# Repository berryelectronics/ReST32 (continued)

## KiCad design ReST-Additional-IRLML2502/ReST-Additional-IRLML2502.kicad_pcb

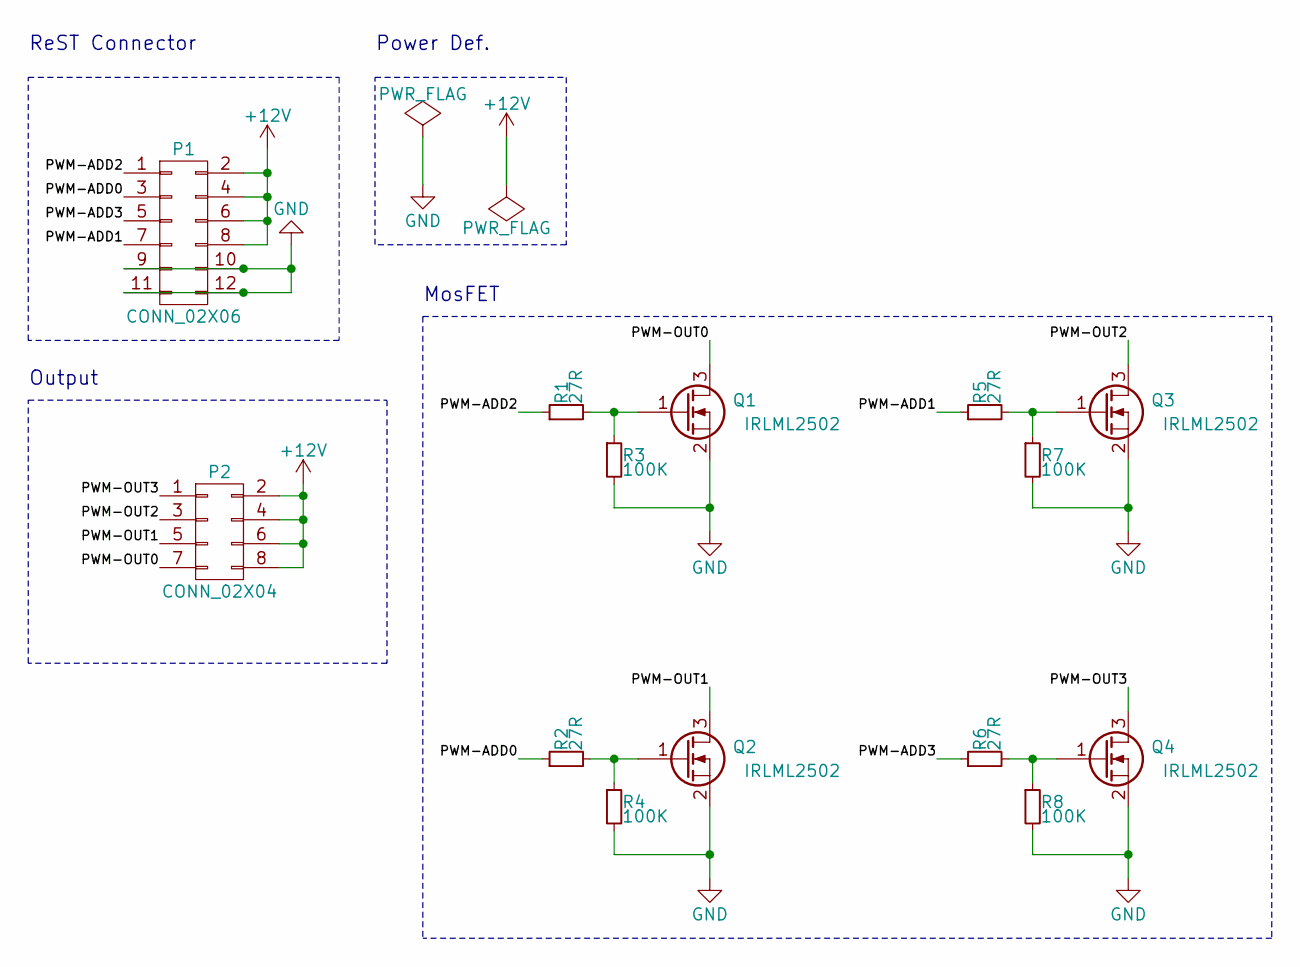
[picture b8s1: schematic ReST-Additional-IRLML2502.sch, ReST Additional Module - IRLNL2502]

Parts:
P1: CONN_02X06; bb02-hp12
P2: CONN_02X04; Pin_Header_Straight_2x04
Q1, Q2, Q3, Q4: IRLML2502; SOT-23
R1, R2, R5, R6: 27R; R_0603_HandSoldering
R3, R4, R7, R8: 100K; R_0603_HandSoldering

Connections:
+12V: P1.2, P1.4, P1.6, P1.8, P2.2, P2.4, P2.6, P2.8
/PWM-ADD0: P1.3, R2.1
/PWM-ADD1: P1.7, R5.1
/PWM-ADD2: P1.1, R1.1
/PWM-ADD3: P1.5, R6.1
/PWM-OUT0: P2.7, Q1.3 (D)
/PWM-OUT1: P2.5, Q2.3 (D)
/PWM-OUT2: P2.3, Q3.3 (D)
/PWM-OUT3: P2.1, Q4.3 (D)
GND: P1.9, P1.10, P1.11, P1.12, Q1.2 (S), Q2.2 (S), Q3.2 (S), Q4.2 (S), R3.2, R4.2, R7.2, R8.2
unnamed: Q1.1 (G), R1.2, R3.1
unnamed: Q2.1 (G), R2.2, R4.1
unnamed: Q3.1 (G), R5.2, R7.1
unnamed: Q4.1 (G), R6.2, R8.1

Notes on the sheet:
ReST Connector
Power Def.
Output
MosFET

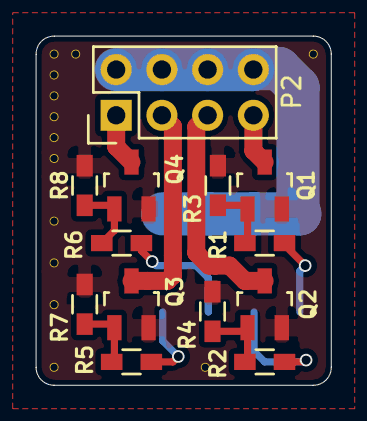
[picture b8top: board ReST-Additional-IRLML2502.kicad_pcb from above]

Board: 2 copper layers, 16.4 x 19.4 mm, 14 parts (1 on the bottom side), 14 nets.

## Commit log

2016-01-24 :space_invader: Added .gitattributes
2016-01-26 Initial Commit
    Added Schematics for Heatbed Module and Mainboard
2016-01-27 Changes Heatbed + Added Driver Board
    Edited Heatbed SMD Footprint from 0805 to 1206, easier to solder for beginners.
    Added Schematic and Netlist for Pololu Driver Board
2016-01-28 Added Libs
2016-01-28 Added all missing Libs.
    You may add them manually.
    Need any suggestion onto how to clean up that library mess. thanks :)
2016-01-29 Layout for Heatbed PCB
    Basic layout for the heatbed pcb is finished. single sided load, so its easier for reflow. need to work on the traces now. size shouldnt change by now.
2016-01-29 Moved Folders + Heatbed PCB Finished
    If there is any problem, please post an issue or write a post on the stm32duino forum. I can assure there is going to be a problem again with the libraries used, would really appreciate it to get som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
2016-01-30 Added Heater Module Schematic + PCB
    Basically its the Heatbed Module but without the fuse (which is going onto the main controller) and without the external VIN, gets power from Pinheader.
    Should be capable of up to 5A if the female pinheader can handle 1A per pin, which seems to be common, but you never know..
2016-01-30 Added Pololu Driver PCB
    Size is 3.5cm * 3.75cm
    Im pretty happy with that size
2016-01-30 Changed minor issues in the Pololu Driver.
    Heatbed wont get much smaller. Finished Dimensions:
    Heatbed: 30,4mm * 47,8mm
    Heater: 29mm * 34,1mm
    Pololu: 36,3mm * 35,2mm
2016-01-30 Added ReST connector to the Mainboard
2016-02-02 Added Additional Module
2016-02-02 Fixed GND Connection on ADD Board
2016-02-02 Saving
2016-02-02 Added Pololu to the Mainboard
2016-02-06 Changes to the mainboard
    removed the pololu connector, added it onboard. added 5V regulator. need to add 3.3V Regulator and more pinout (Bluetooth, SWD, Boot0/Boot1 and more)
2016-02-08 Added Buck & Power Pins
    Buck Converter Added (Still need work on Diode, have to do the math later)
    Power Distribution Pins added (4 Pins of GND 12V 5V 3V3 each) for convenience (Leds and whatnot)
2016-02-08 Added A possible Pinout Table + Removed Pololu Driver Board
2016-02-08 Added PDF
2016-02-08 Added Addition Pinout
2016-02-15 Changed Additional-Board and Pinout
    Sooo... I thought adding multiple Additional Module Boards would be bit much. Looked back at some older projects of mine and thought that using something like the uln2803 would be pretty neat (like 8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
    But using that one resultet in removing many extra pinouts, leaving with only 5 unused pins which will be broken out extra. This may change when the lcd pinout is finished. adding extra pinout for th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
    Also missing: I2C E
2016-02-15 Changed pin naming on excel table
2016-02-15 Added Pin Def. on Mainboard + EEPROM
    FInishing of for today:
    copied the pin def. of the mainboard and added a eeprom (AT24C128)
2016-02-21 Changed ADD Board to use less Pins
    Now only 4 Channels, but everyone ~0.6A capable
2016-02-21 Added LCD 8080 Pinout
2016-02-21 Added Pinout PDF
2016-02-21 Final Version of Main Controller Schematic
2016-02-22 Finishing Footprint connection for Mainboard
2016-02-22 Loaded Netlist into PCB and laid it all out
2016-02-27 PRE-RELEASE Rev. A!
    Yay. I managed to finish the Main PCB over the night, must say, Im happy with it. Things that changed since the last release:
    Heater:
    -Heater Module uses less Pins
    - Much smaller Design now
    Heatbed & Additional Module:
    -Changed distance from Edge to first Pin from 2.5mm to 2mm (will be changed on other boards too)
2016-02-27 Added Images and PDF's
    + Silkscreening
2016-02-27 Added Heatbed 3D Images
2016-02-27 Added PDF for Pinout
    +removed images from logo
2016-02-28 Added Mounting Holes to all Modules
2016-02-28 Missing Mainboard Top PNG
2016-02-28 Added files via upload
2016-02-28 PNG Mainboard
2016-02-28 Added BOM and changed Oscillator to Crystal
2016-02-28 Added Missing Screw Holes on main
2016-02-28 Added SD Card Schematic
2016-03-01 Removed unnecessary Libs and finished SD Card Module
2016-03-05 Finally removed all unnecessary Libs and added Heatsink for 5V Regulator
2016-03-05 Added IRLML2502 Module and added Ground vias everywhere
2016-03-06 Added BOM for all Items + suggested Links
2016-03-06 Added relative paths and linked footprint to a extra repo
    hope i finally fixed the problem with missing libs. will try to add the
    3d views, too
2016-03-07 Finished PCB design, notations and silkscreen
    gonna work to finish a combined design for cheaper pcb cost and put
    everything i need into the bom
2016-03-09 Final release
2016-03-09 Finished Combined PCB and Gerber files
    Combined pcb fits on 10x10cm, breakable and gerbers are finished for elecrow order. will order everything this weekend, lets see if it works.
2016-05-13 Reworked Modules to sit ontop of the mainboard
2016-05-14 Mainboard structure made and most modules finished
2016-05-15 autosave
2016-05-16 Rework. missing screws but everything else fits
2016-05-16 Save of work
2016-05-22 finishing touches on Heater and Stepper Modules
2016-05-27 minor changes
2016-05-30 Changes in Heatbed and Heater + F1 and F4 Pinout table with functions
2016-06-23 temp push
2016-06-26 Hierarchical Schematic finished. Progress on PCB Layout
2016-06-26 Saved
2016-06-26 extra_output saved
2016-06-27 started routing
2016-07-10 Mostly finished with main PCB. Only need to work the High Current Stuff out. On Vacation for now
2016-07-26 electrically finished. in the works of the silkscreening.
    Schematic for SD Card Adapter and a RepRapDiscount-Adapter in the works. but not in this commit
2016-07-26 Create gh-pages branch via GitHub
2016-07-26 final release of the main PCB
2016-07-26 removed copper and solder mask around screw holes
2016-07-26 updated SD Card module
2016-07-26 Final Release
    With Mainboard, SD Card Adapter and Adapter for a RepRapDiscount Full Graphic Smart Controller
    The SD Card Socket can be soldered on the front or on the back, so that the user can insert the card either from top or from the botton, depending on how the controller is mounted.
2016-07-26 forgot naming of the connector in the lcd adapter
2016-07-26 added ESP-01 Support
    Afterthought, completely forgot about it
2016-07-26 Added ESP To the Mainboard
2016-07-27 added missing usb pullup
2016-07-27 minor changes to values of components and footprints. added two leds for both 12V Rails.
2016-07-28 final release. PCBs ordered
2016-09-22 changes in footprints of heater part and misc. stuff
2016-09-23 Heater: moved limiting resistor to the IO Pin, changed footprints
2016-09-23 changed extra output schematic
    added 3->5V level transtor. changed footprints. changed resistor
    footprints.
2016-09-24 changed extra output circuit, removed 3.3V Buck and replaced with LDO
2016-09-24 changed 3.3V LDO due to symbol errors
2016-09-24 importet new net
2016-09-24 now using a 74ahc125 instead of transistor logic for level conversion
